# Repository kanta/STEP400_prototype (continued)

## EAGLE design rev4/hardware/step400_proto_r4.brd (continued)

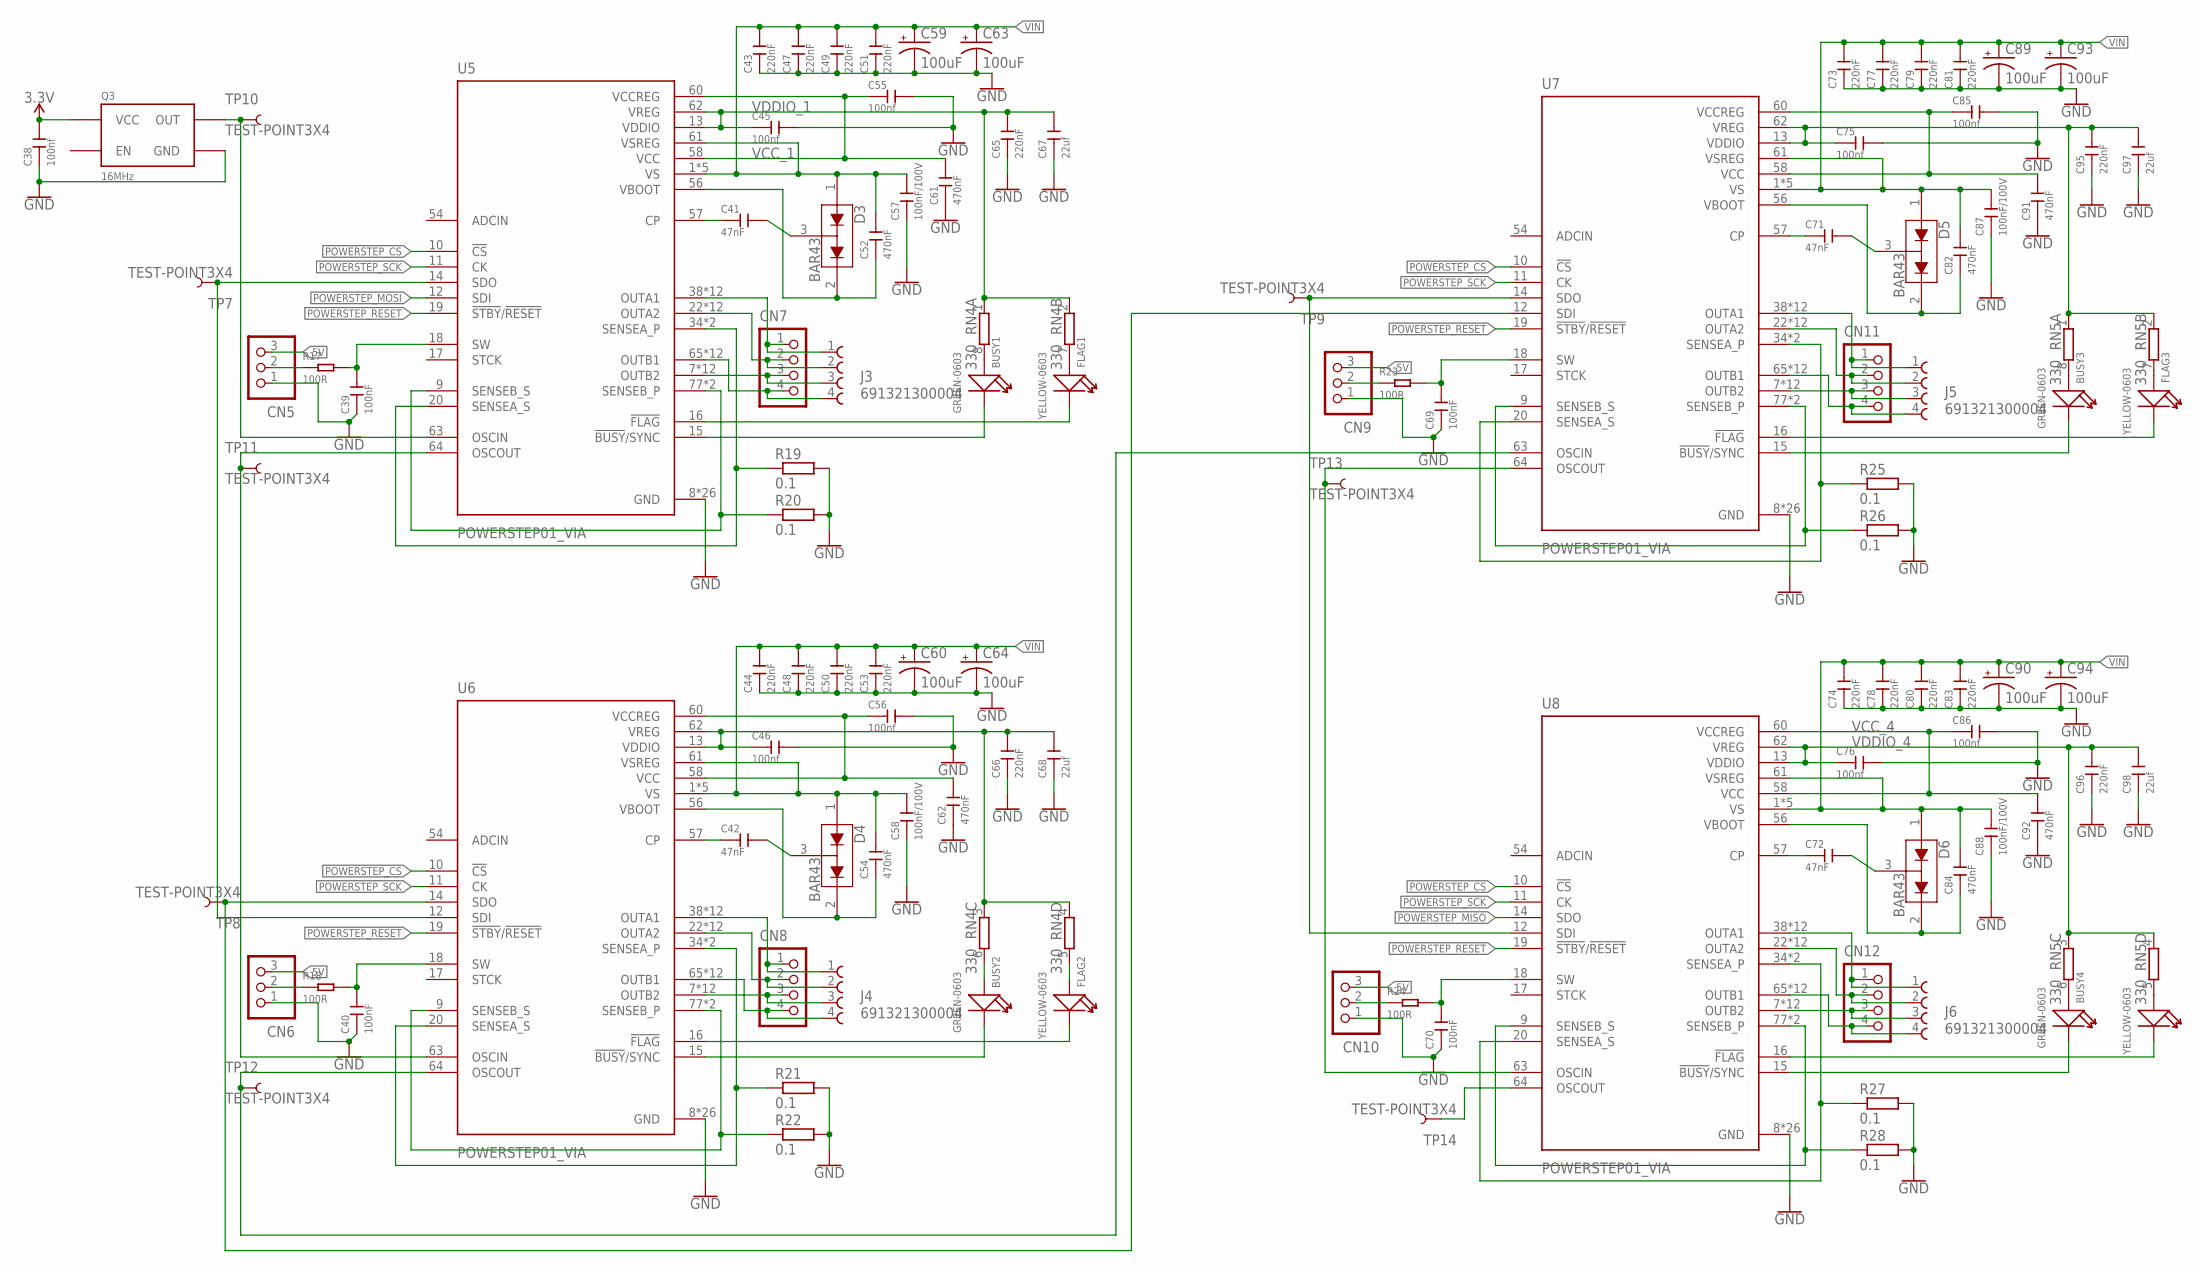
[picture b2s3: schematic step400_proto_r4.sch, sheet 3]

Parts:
BUSY1, BUSY2, BUSY3, BUSY4: GREEN-0603; LED-0603
C38, C45, C46, C55, C56, C75, C76, C85, C86: 100nf; C0402
C39, C40, C69, C70: 100nF; C0402
C41, C42, C71, C72: 47nF; C0805
C43, C44, C47, C48, C49, C50, C51, C53, C73, C74, C77, C78, C79, C80, C81, C83: 220nF; C0805
C52, C54, C61, C62, C82, C84, C91, C92: 470nF; C0603
C57, C58, C87, C88: 100nF/100V; C0805
C59, C60, C63, C64, C89, C90, C93, C94: 100uF; E5-10,5
C65, C66, C95, C96: 220nF; C0402
C67, C68, C97, C98: 22uf; C0805
CN5, CN6, CN9, CN10: B3B-XASK-1
CN7, CN8, CN11, CN12: B4B-XASK-1
D3, D4, D5, D6: BAR43; SOT23-3
FLAG1, FLAG2, FLAG3, FLAG4: YELLOW-0603; LED-0603
J3, J4, J5, J6: 691321300004
Q3: 16MHz; SG5032
R17, R18, R23, R24: 100R; R0603
R19, R20, R21, R22, R25, R26, R27, R28: 0.1; RESC6332X71N
RN4, RN5: 330; CAY16_LONG_W
TP7, TP8, TP9, TP10, TP11, TP12, TP13, TP14: TEST-POINT3X4; PAD.03X.04
U5, U6, U7, U8: POWERSTEP01_VIA; IC_POWERSTEP01_VIA

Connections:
3.3V: C38.2, Q3.4 (VCC); also elsewhere on the board
5V: CN5.3, CN6.3, CN9.3, CN10.3; also elsewhere on the board
GND: C38.1, C39.1, C40.1, C43.1, C44.1, C45.2, C46.2, C47.1, C48.1, C49.1, C50.1, C51.1, C53.1, C55.2, C56.2, C57.1, C58.1, C59.-, C60.-, C61.1, C62.1, C63.-, C64.-, C65.1, C66.1, C67.1, C68.1, C69.1, C70.1, C73.1, C74.1, C75.2, C76.2, C77.1, C78.1, C79.1, C80.1, C81.1, C83.1, C85.2, C86.2, C87.1, C88.1, C89.-, C90.-, C91.1, C92.1, C93.-, C94.-, C95.1, C96.1, C97.1, C98.1, CN5.1, CN6.1, CN9.1, CN10.1, Q3.2 (GND), R19.2, R20.2, R21.2, R22.2, R25.2, R26.2, R27.2, R28.2, U5.8 (GND), U5.21 (GND), U5.59 (GND), U5.EPAD9 (GND), U5.EPAD9_VIA1 (GND), U5.EPAD9_VIA2 (GND), U5.EPAD9_VIA3 (GND), U5.EPAD9_VIA4 (GND), U5.EPAD9_VIA5 (GND), U5.EPAD9_VIA6 (GND), U5.EPAD9_VIA7 (GND), U5.EPAD9_VIA8 (GND), U5.EPAD9_VIA9 (GND), U5.EPAD9_VIA10 (GND), U5.EPAD9_VIA11 (GND), U5.EPAD9_VIA12 (GND), U5.EPAD9_VIA13 (GND), U5.EPAD9_VIA14 (GND), U5.EPAD9_VIA15 (GND), U5.EPAD9_VIA16 (GND), U5.EPAD9_VIA17 (GND), U5.EPAD9_VIA18 (GND), U5.EPAD9_VIA19 (GND), U5.EPAD9_VIA20 (GND), U5.EPAD9_VIA21 (GND), U5.EPAD9_VIA22 (GND), U6.8 (GND), U6.21 (GND), U6.59 (GND), U6.EPAD9 (GND), U6.EPAD9_VIA1 (GND), U6.EPAD9_VIA2 (GND), U6.EPAD9_VIA3 (GND), U6.EPAD9_VIA4 (GND), U6.EPAD9_VIA5 (GND), U6.EPAD9_VIA6 (GND), U6.EPAD9_VIA7 (GND), U6.EPAD9_VIA8 (GND), U6.EPAD9_VIA9 (GND), U6.EPAD9_VIA10 (GND), U6.EPAD9_VIA11 (GND), U6.EPAD9_VIA12 (GND), U6.EPAD9_VIA13 (GND), U6.EPAD9_VIA14 (GND), U6.EPAD9_VIA15 (GND), U6.EPAD9_VIA16 (GND), U6.EPAD9_VIA17 (GND), U6.EPAD9_VIA18 (GND), U6.EPAD9_VIA19 (GND), U6.EPAD9_VIA20 (GND), U6.EPAD9_VIA21 (GND), U6.EPAD9_VIA22 (GND), U7.8 (GND), U7.21 (GND), U7.59 (GND), U7.EPAD9 (GND), U7.EPAD9_VIA1 (GND), U7.EPAD9_VIA2 (GND), U7.EPAD9_VIA3 (GND), U7.EPAD9_VIA4 (GND), U7.EPAD9_VIA5 (GND), U7.EPAD9_VIA6 (GND), U7.EPAD9_VIA7 (GND), U7.EPAD9_VIA8 (GND), U7.EPAD9_VIA9 (GND), U7.EPAD9_VIA10 (GND), U7.EPAD9_VIA11 (GND), U7.EPAD9_VIA12 (GND), U7.EPAD9_VIA13 (GND), U7.EPAD9_VIA14 (GND), U7.EPAD9_VIA15 (GND), U7.EPAD9_VIA16 (GND), U7.EPAD9_VIA17 (GND), U7.EPAD9_VIA18 (GND), U7.EPAD9_VIA19 (GND), U7.EPAD9_VIA20 (GND), U7.EPAD9_VIA21 (GND), U7.EPAD9_VIA22 (GND), U8.8 (GND), U8.21 (GND), U8.59 (GND), U8.EPAD9 (GND), U8.EPAD9_VIA1 (GND), U8.EPAD9_VIA2 (GND), U8.EPAD9_VIA3 (GND), U8.EPAD9_VIA4 (GND), U8.EPAD9_VIA5 (GND), U8.EPAD9_VIA6 (GND), U8.EPAD9_VIA7 (GND), U8.EPAD9_VIA8 (GND), U8.EPAD9_VIA9 (GND), U8.EPAD9_VIA10 (GND), U8.EPAD9_VIA11 (GND), U8.EPAD9_VIA12 (GND), U8.EPAD9_VIA13 (GND), U8.EPAD9_VIA14 (GND), U8.EPAD9_VIA15 (GND), U8.EPAD9_VIA16 (GND), U8.EPAD9_VIA17 (GND), U8.EPAD9_VIA18 (GND), U8.EPAD9_VIA19 (GND), U8.EPAD9_VIA20 (GND), U8.EPAD9_VIA21 (GND), U8.EPAD9_VIA22 (GND); also elsewhere on the board
unnamed: TP14.P$1, U8.64 (OSCOUT)
unnamed: BUSY1.+, RN4.8 (2)
unnamed: CN5.2, R17.1
unnamed: C39.2, R17.2, U5.18 (SW)
unnamed: C40.2, R18.2, U6.18 (SW)
unnamed: CN6.2, R18.1
unnamed: C69.2, R23.2, U7.18 (SW)
unnamed: CN9.2, R23.1
unnamed: FLAG1.+, RN4.7 (2)
unnamed: C70.2, R24.2, U8.18 (SW)
unnamed: C41.2, D3.3 (COM)
unnamed: C41.1, U5.57 (CP)
unnamed: CN10.2, R24.1
unnamed: BUSY2.+, RN4.6 (2)
unnamed: FLAG2.+, RN4.5 (2)
unnamed: FLAG1.-, U5.16 (!FLAG)
unnamed: BUSY1.-, U5.15 (!BUSY!/SYNC)
unnamed: R20.1, U5.9 (SENSEB_S), U5.77 (SENSEB_P), U5.82 (SENSEB_P)
unnamed: R19.1, U5.20 (SENSEA_S), U5.34 (SENSEA_P), U5.39 (SENSEA_P)
unnamed: CN7.1, J3.1, U5.38 (OUTA1), U5.42 (OUTA1), U5.53 (OUTA1), U5.EPAD4 (OUTA1), U5.EPAD4_VIA1 (OUTA1), U5.EPAD4_VIA2 (OUTA1), U5.EPAD4_VIA3 (OUTA1), U5.EPAD4_VIA4 (OUTA1), U5.EPAD4_VIA5 (OUTA1), U5.EPAD4_VIA6 (OUTA1), U5.EPAD4_VIA7 (OUTA1), U5.EPAD4_VIA8 (OUTA1)
unnamed: CN7.2, J3.2, U5.22 (OUTA2), U5.33 (OUTA2), U5.37 (OUTA2), U5.EPAD3 (OUTA2), U5.EPAD3_VIA1 (OUTA2), U5.EPAD3_VIA2 (OUTA2), U5.EPAD3_VIA3 (OUTA2), U5.EPAD3_VIA4 (OUTA2), U5.EPAD3_VIA5 (OUTA2), U5.EPAD3_VIA6 (OUTA2), U5.EPAD3_VIA7 (OUTA2), U5.EPAD3_VIA8 (OUTA2)
unnamed: TP7.P$1, U5.14 (SDO), U6.12 (SDI)
unnamed: CN7.3, J3.3, U5.7 (OUTB2), U5.81 (OUTB2), U5.85 (OUTB2), U5.EPAD8 (OUTB2), U5.EPAD8_VIA1 (OUTB2), U5.EPAD8_VIA2 (OUTB2), U5.EPAD8_VIA3 (OUTB2), U5.EPAD8_VIA4 (OUTB2), U5.EPAD8_VIA5 (OUTB2), U5.EPAD8_VIA6 (OUTB2), U5.EPAD8_VIA7 (OUTB2), U5.EPAD8_VIA8 (OUTB2)
unnamed: CN7.4, J3.4, U5.65 (OUTB1), U5.76 (OUTB1), U5.80 (OUTB1), U5.EPAD7 (OUTB1), U5.EPAD7_VIA1 (OUTB1), U5.EPAD7_VIA2 (OUTB1), U5.EPAD7_VIA3 (OUTB1), U5.EPAD7_VIA4 (OUTB1), U5.EPAD7_VIA5 (OUTB1), U5.EPAD7_VIA6 (OUTB1), U5.EPAD7_VIA7 (OUTB1), U5.EPAD7_VIA8 (OUTB1)
unnamed: C42.2, D4.3 (COM)
unnamed: C42.1, U6.57 (CP)
unnamed: BUSY3.+, RN5.8 (2)
unnamed: FLAG3.+, RN5.7 (2)
unnamed: FLAG2.-, U6.16 (!FLAG)
unnamed: BUSY2.-, U6.15 (!BUSY!/SYNC)
unnamed: R22.1, U6.9 (SENSEB_S), U6.77 (SENSEB_P), U6.82 (SENSEB_P)
unnamed: R21.1, U6.20 (SENSEA_S), U6.34 (SENSEA_P), U6.39 (SENSEA_P)
unnamed: TP12.P$1, U6.64 (OSCOUT), U7.63 (OSCIN)
unnamed: CN8.1, J4.1, U6.38 (OUTA1), U6.42 (OUTA1), U6.53 (OUTA1), U6.EPAD4 (OUTA1), U6.EPAD4_VIA1 (OUTA1), U6.EPAD4_VIA2 (OUTA1), U6.EPAD4_VIA3 (OUTA1), U6.EPAD4_VIA4 (OUTA1), U6.EPAD4_VIA5 (OUTA1), U6.EPAD4_VIA6 (OUTA1), U6.EPAD4_VIA7 (OUTA1), U6.EPAD4_VIA8 (OUTA1)
unnamed: CN8.2, J4.2, U6.22 (OUTA2), U6.33 (OUTA2), U6.37 (OUTA2), U6.EPAD3 (OUTA2), U6.EPAD3_VIA1 (OUTA2), U6.EPAD3_VIA2 (OUTA2), U6.EPAD3_VIA3 (OUTA2), U6.EPAD3_VIA4 (OUTA2), U6.EPAD3_VIA5 (OUTA2), U6.EPAD3_VIA6 (OUTA2), U6.EPAD3_VIA7 (OUTA2), U6.EPAD3_VIA8 (OUTA2)
unnamed: CN8.3, J4.3, U6.7 (OUTB2), U6.81 (OUTB2), U6.85 (OUTB2), U6.EPAD8 (OUTB2), U6.EPAD8_VIA1 (OUTB2), U6.EPAD8_VIA2 (OUTB2), U6.EPAD8_VIA3 (OUTB2), U6.EPAD8_VIA4 (OUTB2), U6.EPAD8_VIA5 (OUTB2), U6.EPAD8_VIA6 (OUTB2), U6.EPAD8_VIA7 (OUTB2), U6.EPAD8_VIA8 (OUTB2)
unnamed: CN8.4, J4.4, U6.65 (OUTB1), U6.76 (OUTB1), U6.80 (OUTB1), U6.EPAD7 (OUTB1), U6.EPAD7_VIA1 (OUTB1), U6.EPAD7_VIA2 (OUTB1), U6.EPAD7_VIA3 (OUTB1), U6.EPAD7_VIA4 (OUTB1), U6.EPAD7_VIA5 (OUTB1), U6.EPAD7_VIA6 (OUTB1), U6.EPAD7_VIA7 (OUTB1), U6.EPAD7_VIA8 (OUTB1)
unnamed: BUSY4.+, RN5.6 (2)
unnamed: C82.1, D5.2 (C2), U7.56 (VBOOT)
unnamed: C71.2, D5.3 (COM)
unnamed: C71.1, U7.57 (CP)
unnamed: FLAG4.+, RN5.5 (2)
unnamed: CN11.4, J5.4, U7.65 (OUTB1), U7.76 (OUTB1), U7.80 (OUTB1), U7.EPAD7 (OUTB1), U7.EPAD7_VIA1 (OUTB1), U7.EPAD7_VIA2 (OUTB1), U7.EPAD7_VIA3 (OUTB1), U7.EPAD7_VIA4 (OUTB1), U7.EPAD7_VIA5 (OUTB1), U7.EPAD7_VIA6 (OUTB1), U7.EPAD7_VIA7 (OUTB1), U7.EPAD7_VIA8 (OUTB1)
unnamed: FLAG3.-, U7.16 (!FLAG)
unnamed: BUSY3.-, U7.15 (!BUSY!/SYNC)
unnamed: R26.1, U7.9 (SENSEB_S), U7.77 (SENSEB_P), U7.82 (SENSEB_P)
unnamed: R25.1, U7.20 (SENSEA_S), U7.34 (SENSEA_P), U7.39 (SENSEA_P)
unnamed: TP8.P$1, U6.14 (SDO), U7.12 (SDI)
unnamed: CN11.1, J5.1, U7.38 (OUTA1), U7.42 (OUTA1), U7.53 (OUTA1), U7.EPAD4 (OUTA1), U7.EPAD4_VIA1 (OUTA1), U7.EPAD4_VIA2 (OUTA1), U7.EPAD4_VIA3 (OUTA1), U7.EPAD4_VIA4 (OUTA1), U7.EPAD4_VIA5 (OUTA1), U7.EPAD4_VIA6 (OUTA1), U7.EPAD4_VIA7 (OUTA1), U7.EPAD4_VIA8 (OUTA1)
unnamed: CN11.2, J5.2, U7.22 (OUTA2), U7.33 (OUTA2), U7.37 (OUTA2), U7.EPAD3 (OUTA2), U7.EPAD3_VIA1 (OUTA2), U7.EPAD3_VIA2 (OUTA2), U7.EPAD3_VIA3 (OUTA2), U7.EPAD3_VIA4 (OUTA2), U7.EPAD3_VIA5 (OUTA2), U7.EPAD3_VIA6 (OUTA2), U7.EPAD3_VIA7 (OUTA2), U7.EPAD3_VIA8 (OUTA2)
unnamed: CN11.3, J5.3, U7.7 (OUTB2), U7.81 (OUTB2), U7.85 (OUTB2), U7.EPAD8 (OUTB2), U7.EPAD8_VIA1 (OUTB2), U7.EPAD8_VIA2 (OUTB2), U7.EPAD8_VIA3 (OUTB2), U7.EPAD8_VIA4 (OUTB2), U7.EPAD8_VIA5 (OUTB2), U7.EPAD8_VIA6 (OUTB2), U7.EPAD8_VIA7 (OUTB2), U7.EPAD8_VIA8 (OUTB2)
unnamed: CN12.4, J6.4, U8.65 (OUTB1), U8.76 (OUTB1), U8.80 (OUTB1), U8.EPAD7 (OUTB1), U8.EPAD7_VIA1 (OUTB1), U8.EPAD7_VIA2 (OUTB1), U8.EPAD7_VIA3 (OUTB1), U8.EPAD7_VIA4 (OUTB1), U8.EPAD7_VIA5 (OUTB1), U8.EPAD7_VIA6 (OUTB1), U8.EPAD7_VIA7 (OUTB1), U8.EPAD7_VIA8 (OUTB1)
unnamed: CN12.3, J6.3, U8.7 (OUTB2), U8.81 (OUTB2), U8.85 (OUTB2), U8.EPAD8 (OUTB2), U8.EPAD8_VIA1 (OUTB2), U8.EPAD8_VIA2 (OUTB2), U8.EPAD8_VIA3 (OUTB2), U8.EPAD8_VIA4 (OUTB2), U8.EPAD8_VIA5 (OUTB2), U8.EPAD8_VIA6 (OUTB2), U8.EPAD8_VIA7 (OUTB2), U8.EPAD8_VIA8 (OUTB2)
unnamed: C84.1, D6.2 (C2), U8.56 (VBOOT)
unnamed: C72.2, D6.3 (COM)
unnamed: C72.1, U8.57 (CP)
unnamed: FLAG4.-, U8.16 (!FLAG)
unnamed: BUSY4.-, U8.15 (!BUSY!/SYNC)
unnamed: R28.1, U8.9 (SENSEB_S), U8.77 (SENSEB_P), U8.82 (SENSEB_P)
unnamed: R27.1, U8.20 (SENSEA_S), U8.34 (SENSEA_P), U8.39 (SENSEA_P)
unnamed: CN12.1, J6.1, U8.38 (OUTA1), U8.42 (OUTA1), U8.53 (OUTA1), U8.EPAD4 (OUTA1), U8.EPAD4_VIA1 (OUTA1), U8.EPAD4_VIA2 (OUTA1), U8.EPAD4_VIA3 (OUTA1), U8.EPAD4_VIA4 (OUTA1), U8.EPAD4_VIA5 (OUTA1), U8.EPAD4_VIA6 (OUTA1), U8.EPAD4_VIA7 (OUTA1), U8.EPAD4_VIA8 (OUTA1)
unnamed: CN12.2, J6.2, U8.22 (OUTA2), U8.33 (OUTA2), U8.37 (OUTA2), U8.EPAD3 (OUTA2), U8.EPAD3_VIA1 (OUTA2), U8.EPAD3_VIA2 (OUTA2), U8.EPAD3_VIA3 (OUTA2), U8.EPAD3_VIA4 (OUTA2), U8.EPAD3_VIA5 (OUTA2), U8.EPAD3_VIA6 (OUTA2), U8.EPAD3_VIA7 (OUTA2), U8.EPAD3_VIA8 (OUTA2)
unnamed: Q3.3 (OUT), TP10.P$1, U5.63 (OSCIN)
unnamed: TP11.P$1, U5.64 (OSCOUT), U6.63 (OSCIN)
unnamed: TP13.P$1, U7.64 (OSCOUT), U8.63 (OSCIN)
unnamed: TP9.P$1, U7.14 (SDO), U8.12 (SDI)
POWERSTEP_CS: U5.10 (!CS), U6.10 (!CS), U7.10 (!CS), U8.10 (!CS); also elsewhere on the board
POWERSTEP_MISO: U8.14 (SDO); also elsewhere on the board
POWERSTEP_MOSI: U5.12 (SDI); also elsewhere on the board
POWERSTEP_RESET: U5.19 (!STBY!/!RESET), U6.19 (!STBY!/!RESET), U7.19 (!STBY!/!RESET), U8.19 (!STBY!/!RESET); also elsewhere on the board
POWERSTEP_SCK: U5.11 (CK), U6.11 (CK), U7.11 (CK), U8.11 (CK); also elsewhere on the board
VBOOT_1: C52.1, D3.2 (C2), U5.56 (VBOOT)
VBOOT_2: C54.1, D4.2 (C2), U6.56 (VBOOT)
VCC_1: C55.1, C61.2, U5.58 (VCC), U5.60 (VCCREG)
VCC_2: C56.1, C62.2, U6.58 (VCC), U6.60 (VCCREG)
VCC_3: C85.1, C91.2, U7.58 (VCC), U7.60 (VCCREG)
VCC_4: C86.1, C92.2, U8.58 (VCC), U8.60 (VCCREG)
VDDIO_1: C45.1, C65.2, C67.2, RN4.1, RN4.2 (1), U5.13 (VDDIO), U5.62 (VREG)
VDDIO_2: C46.1, C66.2, C68.2, RN4.3 (1), RN4.4 (1), U6.13 (VDDIO), U6.62 (VREG)
VDDIO_3: C75.1, C95.2, C97.2, RN5.1, RN5.2 (1), U7.13 (VDDIO), U7.62 (VREG)
VDDIO_4: C76.1, C96.2, C98.2, RN5.3 (1), RN5.4 (1), U8.13 (VDDIO), U8.62 (VREG)
VIN: C43.2, C44.2, C47.2, C48.2, C49.2, C50.2, C51.2, C52.2, C53.2, C54.2, C57.2, C58.2, C59.+, C60.+, C63.+, C64.+, C73.2, C74.2, C77.2, C78.2, C79.2, C80.2, C81.2, C82.2, C83.2, C84.2, C87.2, C88.2, C89.+, C90.+, C93.+, C94.+, D3.1 (A1), D4.1 (A1), D5.1 (A1), D6.1 (A1), U5.1 (VS), U5.23 (VS), U5.43 (VS), U5.55 (VS), U5.61 (VSREG), U5.66 (VS), U6.1 (VS), U6.23 (VS), U6.43 (VS), U6.55 (VS), U6.61 (VSREG), U6.66 (VS), U7.1 (VS), U7.23 (VS), U7.43 (VS), U7.55 (VS), U7.61 (VSREG), U7.66 (VS), U8.1 (VS), U8.23 (VS), U8.43 (VS), U8.55 (VS), U8.61 (VSREG), U8.66 (VS); also elsewhere on the board

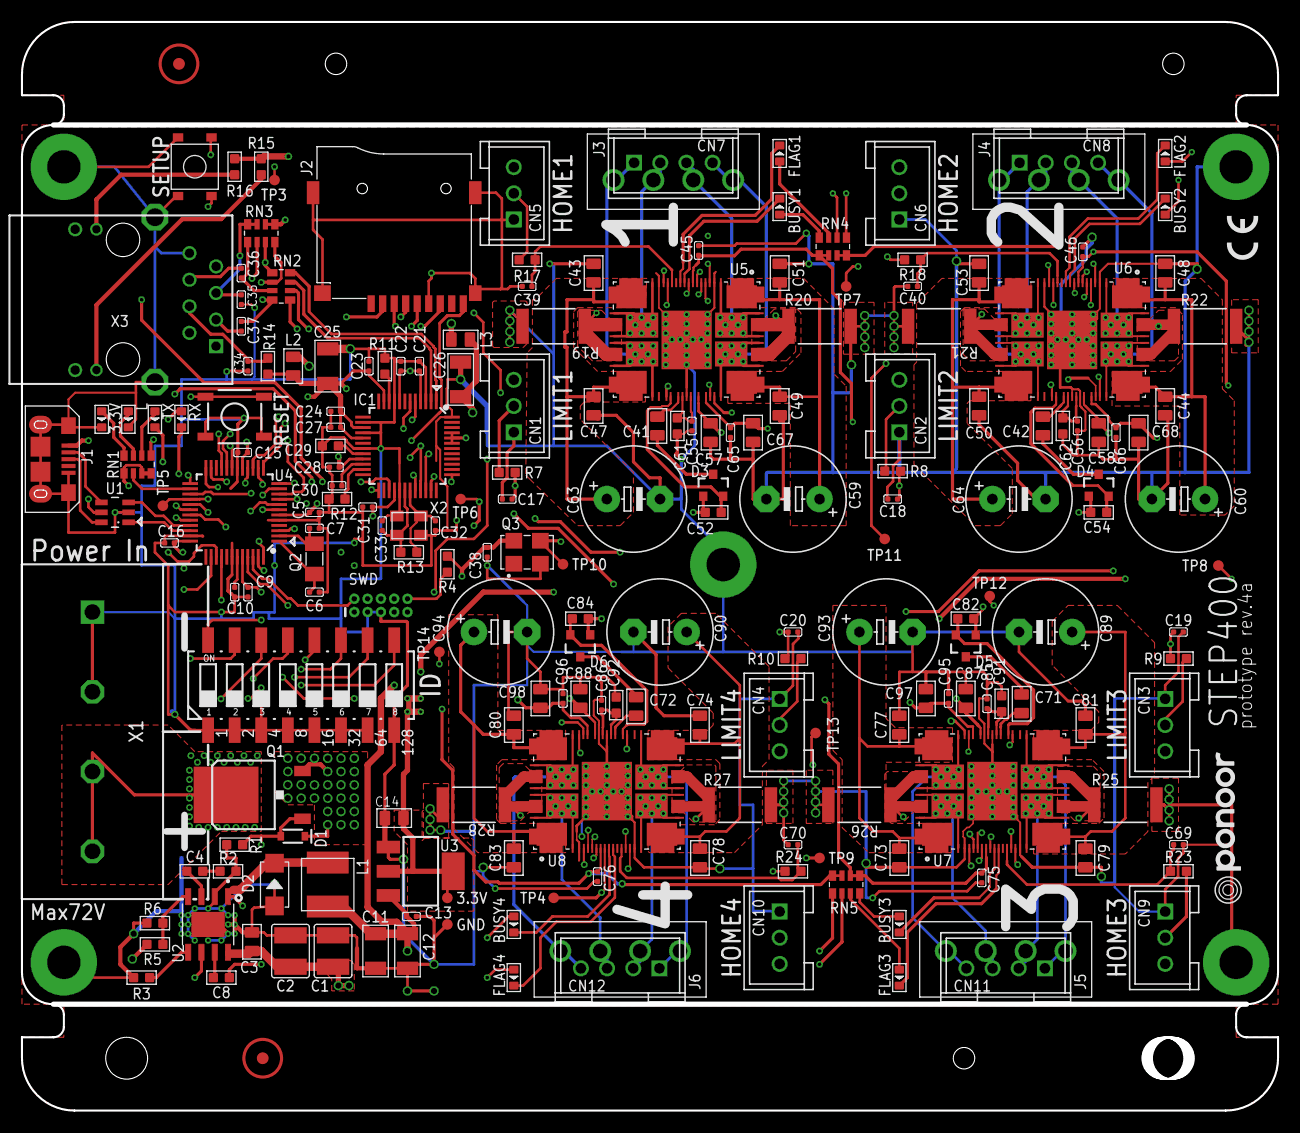
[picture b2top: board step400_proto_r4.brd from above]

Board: 4 copper layers, 120.0 x 104.0 mm, 212 parts (0 on the bottom side), 158 nets.

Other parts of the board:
U$1: PONOOR_TEXT_15MM
U$2, U$3: FIDUCIAL_MARKER_PBAN
U$4: CE_3MM

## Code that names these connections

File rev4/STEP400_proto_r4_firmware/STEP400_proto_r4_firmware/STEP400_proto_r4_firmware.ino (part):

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#define ledPin	13u
const uint8_t dipSwPin[8] = { A5,SCL,7u,SDA,2u,9u,3u,0u };
const uint8_t limitSwPin[4] = { 1u,5u,8u,A1 };
#define SD_CS_PIN	4u
#define SD_DETECT_PIN   A4
#define SETUP_SW_PIN    31u

#define NUM_OF_MOTOR   (4)
#define POWERSTEP_MISO	6u	// D6 /SERCOM3/PAD[2] miso
#define POWERSTEP_MOSI	11u	// D11/SERCOM3/PAD[0] mosi
#define POWERSTEP_SCK	12u	// D12/SERCOM3/PAD[3] sck
SPIClass powerStepSPI(&sercom3, POWERSTEP_MISO, POWERSTEP_SCK, POWERSTEP_MOSI, SPI_PAD_0_SCK_3, SERCOM_RX_PAD_2);// MISO/SCK/MOSI pins

#define POWERSTEP_CS_PIN A0
#define POWERSTEP_RESET_PIN A2
powerSTEP stepper[] = {
    powerSTEP(3, POWERSTEP_CS_PIN, POWERSTEP_RESET_PIN),
    powerSTEP(2, POWERSTEP_CS_PIN, POWERSTEP_RESET_PIN),
    powerSTEP(1, POWERSTEP_CS_PIN, POWERSTEP_RESET_PIN),
    powerSTEP(0, POWERSTEP_CS_PIN, POWERSTEP_RESET_PIN)
};

#define MOTOR_ID_ALL    255
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void setup() {
    //setUSBPriority();
    pinMode(ledPin, OUTPUT);
    pinMode(SD_CS_PIN, OUTPUT);
    pinMode(W5500_RESET_PIN, OUTPUT);
    pinMode(SD_DETECT_PIN, INPUT_PULLUP);
    pinMode(SETUP_SW_PIN, INPUT_PULLUP);

    for (auto i=0; i < NUM_OF_MOTOR; i++)
    {
        pinMode(limitSwPin[i], INPUT_PULLUP);
    }

    pinMode(POWERSTEP_RESET_PIN, OUTPUT);
    pinMode(POWERSTEP_CS_PIN, OUTPUT);
    pinMode(POWERSTEP_MOSI, OUTPUT);
    pinMode(POWERSTEP_MISO, INPUT);
    pinMode(POWERSTEP_SCK, OUTPUT);
    digitalWrite(POWERSTEP_RESET_PIN, HIGH);
    digitalWrite(POWERSTEP_RESET_PIN, LOW);
    delay(10);
    digitalWrite(POWERSTEP_RESET_PIN, HIGH);
    digitalWrite(POWERSTEP_CS_PIN, HIGH);
    powerStepSPI.begin();
    pinPeripheral(POWERSTEP_MOSI, PIO_SERCOM_ALT);
    pinPeripheral(POWERSTEP_SCK, PIO_SERCOM_ALT);
    pinPeripheral(POWERSTEP_MISO, PIO_SERCOM_ALT);
    powerStepSPI.setDataMode(SPI_MODE3);
    
    loadConfig();
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
void checkSetupSw() {
    static boolean lastSetupSwState = false;
    if ( digitalRead(SETUP_SW_PIN) != lastSetupSwState )
    {
        lastSetupSwState = !lastSetupSwState;
        sendOneInt("/setupSw", !lastSetupSwState);
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
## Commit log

2020-04-17 fixed some bugs and constants name of PowerSTEP01 Library
2020-06-17 added /busy /sw /dir report. change spd->speed for osc messeages
2020-06-17 removed minSpeed from speedProfile messeages, some STATUS debugging.
2020-07-10 small modifications for .ino
2020-07-13 Updated .ino, mosty imported from STEP800_proto_r3
2020-07-13 Update the current mode functions. FixedOCD_TH and STALL_TH bit length.
2020-07-14 Updated TVAL and KVAL manegement
2020-07-14 Added limit switch functions
2020-07-22 Max example updated. and some firmware default value updated.
2020-07-27 Added the schematics PDF, updated the Max example patch.
2020-07-29 Added /getFullstepSpeed messeage, and changed the default value of FS_SPD.
2020-08-13 fixed some mistakes in maxpat
2020-08-21 added BEMF compensation and decay mode setting commands
2020-08-26 split one long .ino file to two of .ino
2020-08-26 Fixed a bug on /getSpeedProfile
2020-08-26 added configtool, contribution of @niimi
2020-08-27 Added some initial values and DNS for config tool
2020-08-27 add css
2020-08-28 Updated config tool css
2020-08-28 added css to configtool
2020-09-04 Fixed to multiple motors
2020-09-07 Add configName
2020-09-09 setup switch test code
2020-09-09 Add bootedMsgEnable, canSendMsgBeforeDestIp, electromagnetBrakeEnable
2020-09-11 Updated Max sample patch
2020-09-17 Added a SD config loader for the firmware side.
2020-09-24 Added the brakeboard design files
2020-09-28 string bug fixed
2020-09-29 Config tool css update
2020-09-30 Added OSC error reports
2020-10-02 Added a watchdog timer, fixed `/booted` message timing
2020-10-21 Added example config.txt
2020-10-23 Added some more example config.txt
